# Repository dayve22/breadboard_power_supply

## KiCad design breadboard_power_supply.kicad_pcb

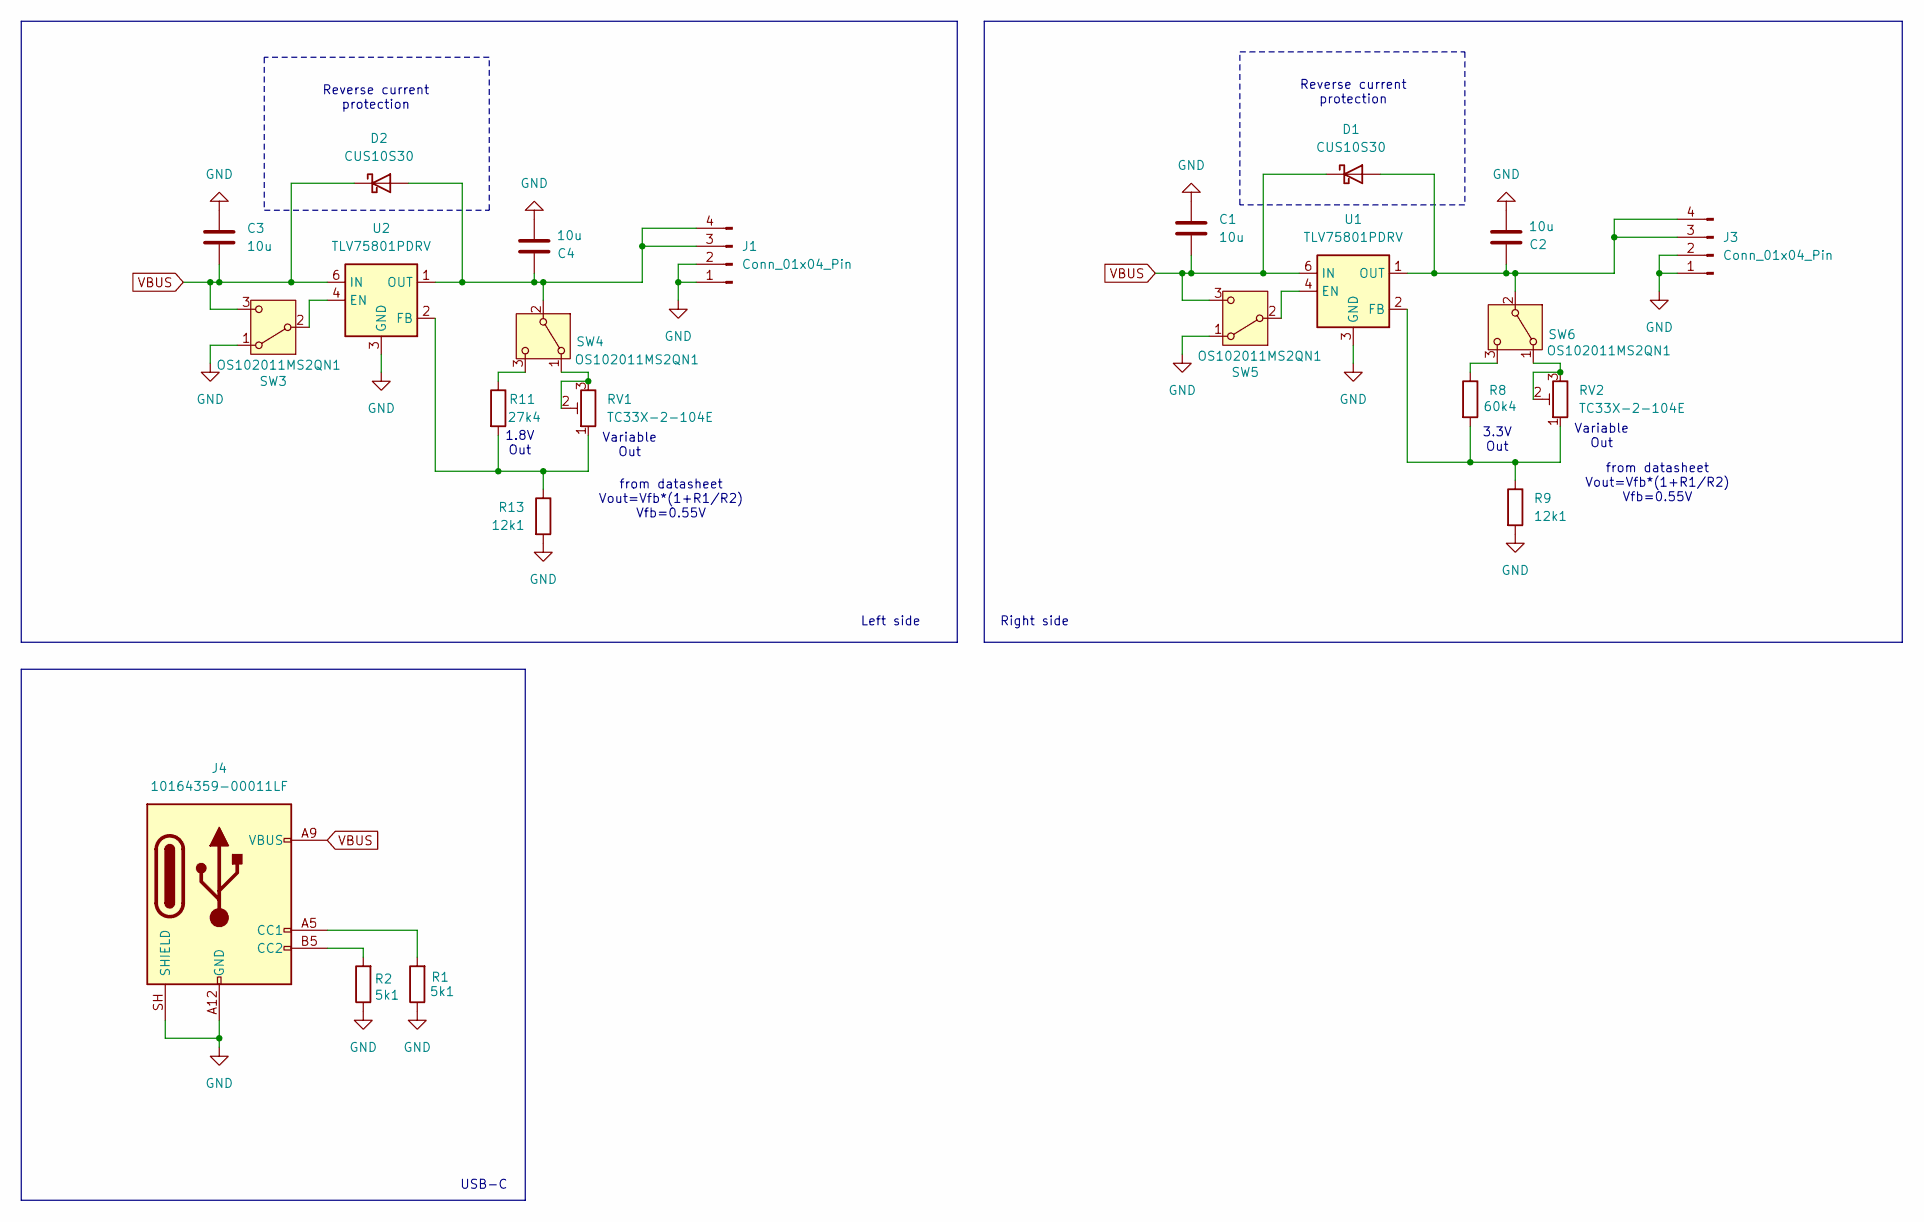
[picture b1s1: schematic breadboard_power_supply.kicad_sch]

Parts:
C1, C2, C3, C4: 10u; C_0805_2012Metric_Pad1.18x1.45mm_HandSolder
D1, D2: CUS10S30; USC_TOS
J1, J3: Conn_01x04_Pin; PinHeader_2x02_P2.54mm_Vertical
J4: 10164359-00011LF; AMPHENOL_10164359-00011LF
R1, R2: 5k1; R_0402_1005Metric_Pad0.72x0.64mm_HandSolder
R8: 60k4; R_0402_1005Metric_Pad0.72x0.64mm_HandSolder
R9, R13: 12k1; R_0402_1005Metric_Pad0.72x0.64mm_HandSolder
R11: 27k4; R_0402_1005Metric_Pad0.72x0.64mm_HandSolder
RV1, RV2: TC33X-2-104E; Potentiometer_Bourns_TC33X_Vertical
SW3, SW4, SW5, SW6: OS102011MS2QN1; SPDT_OS102011_CNK
U1, U2: TLV75801PDRV; WSON-6-1EP_2x2mm_P0.65mm_EP1x1.6mm

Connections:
GND: C1.1, C2.2, C3.1, C4.2, J1.1, J1.2, J3.1, J3.2, J4.A12 (GND), J4.B12 (GND), J4.SH (SHIELD), R1.1, R2.1, R9.2, R13.2, SW3.1 (A), SW5.1 (A), U1.3 (GND), U1.7 (GND), U2.3 (GND), U2.7 (GND)
unnamed: C2.1, D1.2 (A), J3.3, J3.4, SW6.2 (B), U1.1 (OUT)
unnamed: C4.1, D2.2 (A), J1.3, J1.4, SW4.2 (B), U2.1 (OUT)
unnamed: J4.A5 (CC1), R1.2
unnamed: J4.B5 (CC2), R2.2
unnamed: SW3.2 (B), U2.4 (EN)
unnamed: RV1.2, RV1.3, SW4.1 (A)
unnamed: R11.1, SW4.3 (C)
unnamed: SW5.2 (B), U1.4 (EN)
unnamed: RV2.2, RV2.3, SW6.1 (A)
unnamed: R8.1, SW6.3 (C)
unnamed: R8.2, R9.1, RV2.1, U1.2 (FB)
unnamed: R11.2, R13.1, RV1.1, U2.2 (FB)
VBUS: C1.2, C3.2, D1.1 (K), D2.1 (K), J4.A9 (VBUS), J4.B9 (VBUS), SW3.3 (C), SW5.3 (C), U1.6 (IN), U2.6 (IN)

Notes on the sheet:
Reverse current protection
Variable Out
Left side
from datasheet Vout=Vfb*(1+R1/R2) Vfb=0.55V
3.3V Out
Right side
1.8V Out
USB-C

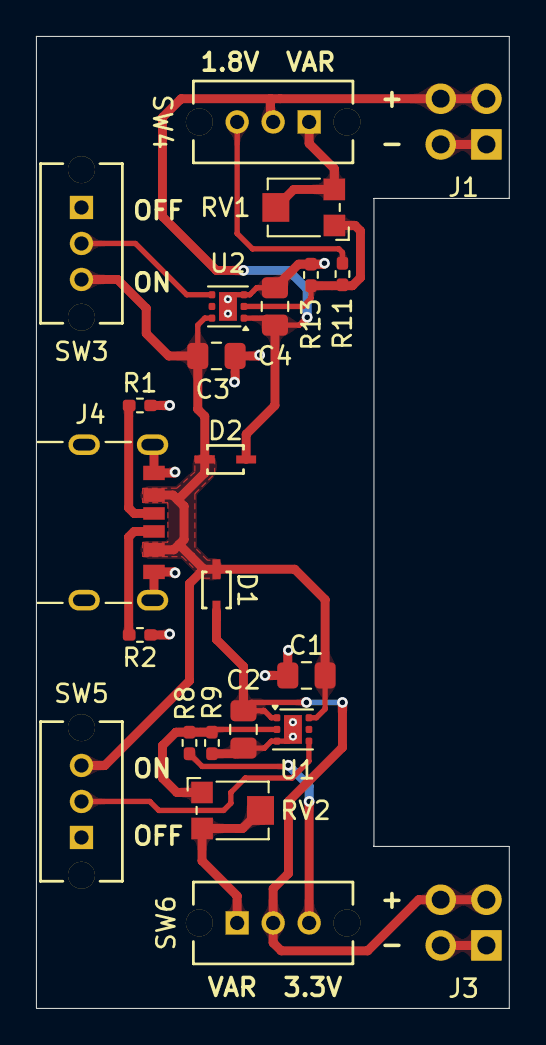
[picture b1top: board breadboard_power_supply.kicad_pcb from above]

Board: 2 copper layers, 26.3 x 54.0 mm, 23 parts (0 on the bottom side), 14 nets.
